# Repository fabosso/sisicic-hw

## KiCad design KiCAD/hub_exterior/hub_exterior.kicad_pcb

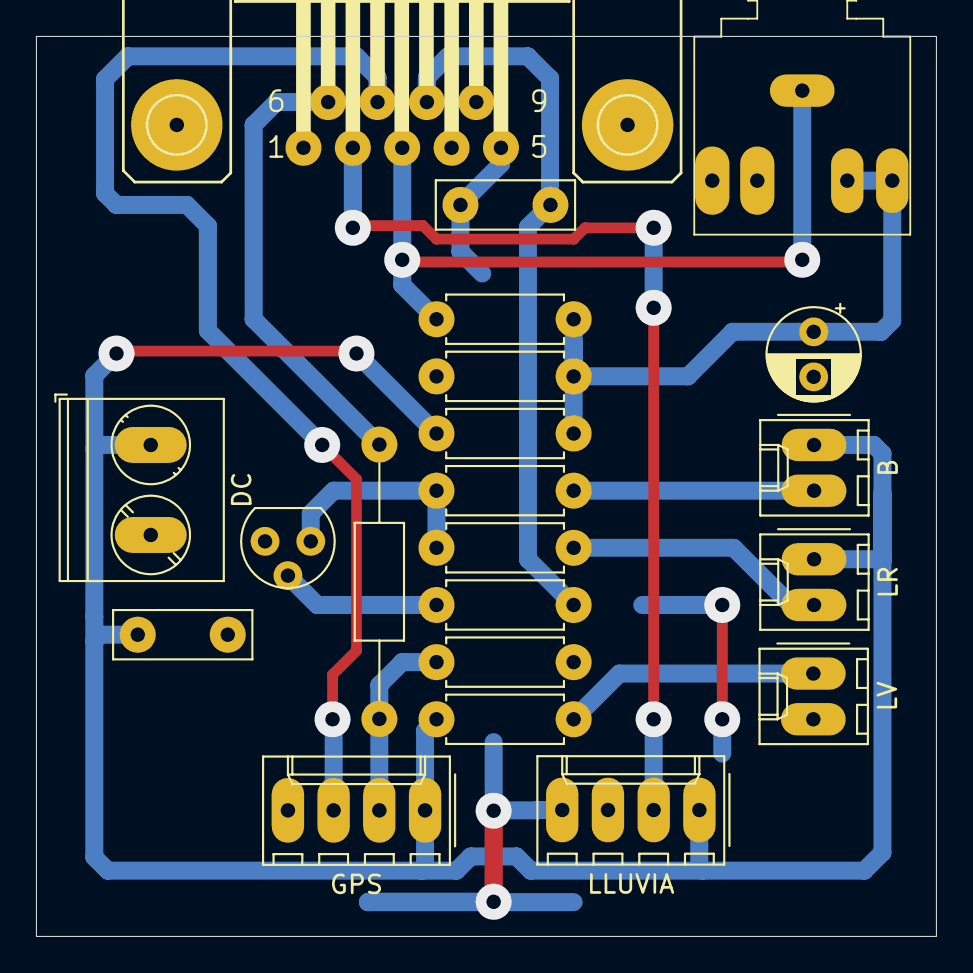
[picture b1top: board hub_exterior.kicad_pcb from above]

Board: 2 copper layers, 50.0 x 50.0 mm, 21 parts (0 on the bottom side), 14 nets.

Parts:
B: BUZZER; Molex_KK-254_AE-6410-02A_1x02_P2.54mm_Vertical
C1, C2: 10nF; C_Disc_D7.5mm_W2.5mm_P5.00mm
C3: 10uF; CP_Radial_D5.0mm_P2.50mm
DC: AK500/2; TerminalBlock_Phoenix_PT-1,5-2-5.0-H_1x02_P5.00mm_Horizontal
GPS: GPS; Molex_KK-254_AE-6410-04A_1x04_P2.54mm_Vertical
LLUVIA: LLUVIA; Molex_KK-254_AE-6410-04A_1x04_P2.54mm_Vertical
LR: LED_ROJO; Molex_KK-254_AE-6410-02A_1x02_P2.54mm_Vertical
LV: LED_VERDE; Molex_KK-254_AE-6410-02A_1x02_P2.54mm_Vertical
Q1: BC337; TO-92
R1, R5, R8, R9: 10kΩ; R_Axial_DIN0207_L6.3mm_D2.5mm_P7.62mm_Horizontal
R2, R4: 470Ω; R_Axial_DIN0207_L6.3mm_D2.5mm_P7.62mm_Horizontal
R3: 1kΩ; R_Axial_DIN0207_L6.3mm_D2.5mm_P7.62mm_Horizontal
R6: 10kΩ; R_Axial_DIN0207_L6.3mm_D2.5mm_P15.24mm_Horizontal
R7: 33Ω; R_Axial_DIN0207_L6.3mm_D2.5mm_P7.62mm_Horizontal
U$1: JACK-STEREO; SPC21348
X1: F09HP

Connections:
+5V: B.2 (S), C2.2 (1), DC.1 (KL), GPS.4 (S), LLUVIA.4 (S), LR.2 (S), R4.1, R8.1
/N$4: R7.2, U$1.P$3 (1), X1.3
/N$8: C1.1, R1.2, X1.8
GND: C1.2, C2.2, C3.2, DC.2 (KL), GPS.1 (S), LLUVIA.1 (S), LLUVIA.2 (S), LV.1 (S), Q1.1 (E), R5.2, R9.2, X1.5
unnamed: C3.1, R7.1, R8.2, R9.1, U$1.P$5 (4), U$1.P$7 (5)
unnamed: LV.2 (S), R4.2
unnamed: Q1.2 (B), R1.1
unnamed: Q1.3 (C), R2.1, R3.1
unnamed: LR.1 (S), R2.2
unnamed: B.1 (S), R3.2
unnamed: GPS.3 (S), R5.1, R6.1
unnamed: R6.2, X1.6
unnamed: LLUVIA.3 (S), X1.2
unnamed: GPS.2 (S), X1.7

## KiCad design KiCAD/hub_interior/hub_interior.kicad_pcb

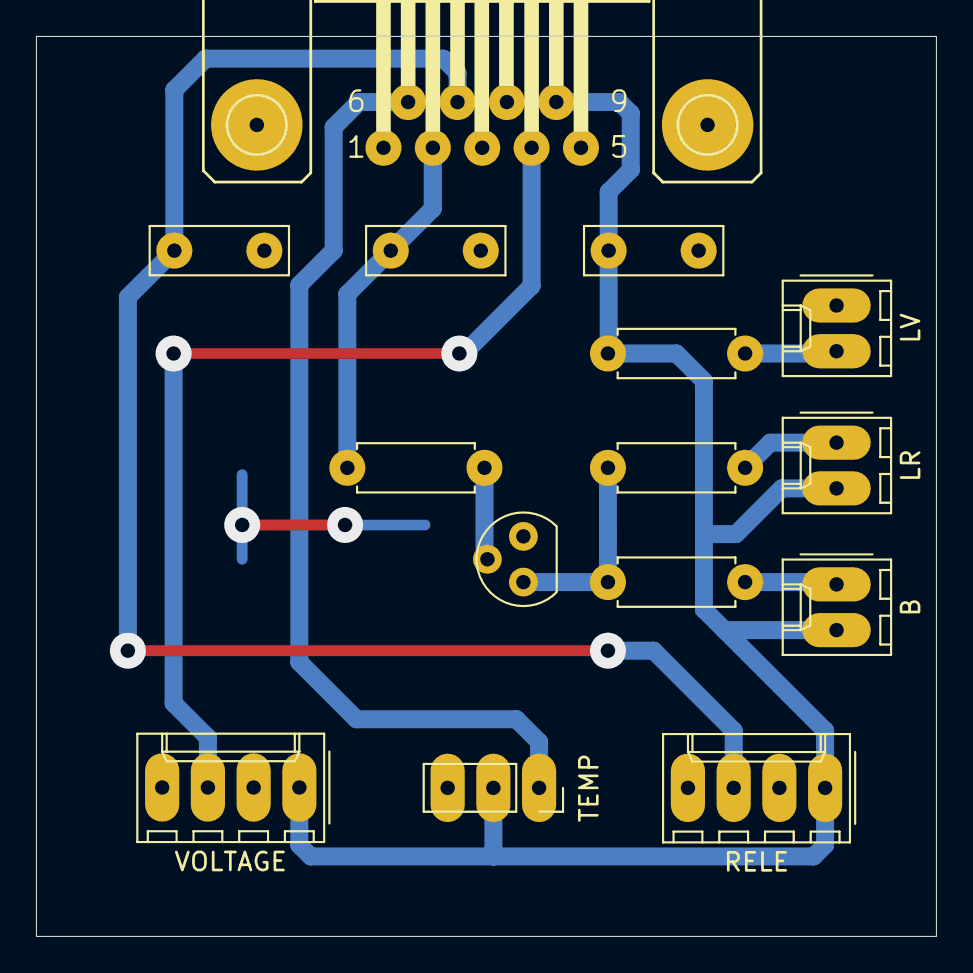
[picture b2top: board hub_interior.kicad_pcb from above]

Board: 2 copper layers, 50.0 x 50.0 mm, 15 parts (0 on the bottom side), 11 nets.

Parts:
B: BUZZER; Molex_KK-254_AE-6410-02A_1x02_P2.54mm_Vertical
C1, C2, C4: 10nF; C_Disc_D7.5mm_W2.5mm_P5.00mm
LR: LED_ROJO; Molex_KK-254_AE-6410-02A_1x02_P2.54mm_Vertical
LV: LED_VERDE; Molex_KK-254_AE-6410-02A_1x02_P2.54mm_Vertical
Q1: BC337; TO-92
R1: 10kΩ; R_Axial_DIN0207_L6.3mm_D2.5mm_P7.62mm_Horizontal
R2: 1kΩ; R_Axial_DIN0207_L6.3mm_D2.5mm_P7.62mm_Horizontal
R3, R4: 470Ω; R_Axial_DIN0207_L6.3mm_D2.5mm_P7.62mm_Horizontal
RELE: 22-23-2041; Molex_KK-254_AE-6410-04A_1x04_P2.54mm_Vertical
TEMP: PINHD-1X3; PinSocket_1x03_P2.54mm_Vertical
VOLTAGE: 22-23-2041; Molex_KK-254_AE-6410-04A_1x04_P2.54mm_Vertical
X1: F09HP

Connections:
+5V: B.1 (S), C2.1, LR.1 (S), R4.1, RELE.4 (S), TEMP.2, VOLTAGE.4 (S), X1.9
GND: C1.2, C2.2, C4.2, LV.2 (S), Q1.1 (E), RELE.1 (S), RELE.3 (S), TEMP.3, VOLTAGE.1 (S), VOLTAGE.3 (S)
unnamed: C1.1, R1.2, X1.2
unnamed: C4.1, RELE.2 (S), X1.7
unnamed: TEMP.1, X1.6
unnamed: LV.1 (S), R4.2
unnamed: Q1.2 (B), R1.1
unnamed: Q1.3 (C), R2.1, R3.1
unnamed: B.2 (S), R2.2
unnamed: LR.2 (S), R3.2
unnamed: VOLTAGE.2 (S), X1.4

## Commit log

2021-03-30 Add files via upload
    Añadidos archivos .brd y .sch
2021-03-30 Add files via upload
    Añadidos .lbr de eagle
2022-07-27 add files hub interior
2022-07-27 add files hub exterior
2022-07-27 add libraries
2022-08-19 Relocations
2022-08-19 Relocation bis
2022-08-19 Update EAGLE files (hub exterior)
2022-08-19 KiCAD and FlatCAM upload files
2022-08-24 rediseño hub interior
2022-08-24 rediseño hub exterior
2022-08-24 añadir software utilizado
2022-08-24 añadida carpeta docs
2022-08-24 engrosado pads hub interior
2022-08-24 engrosado pads hub exterior
